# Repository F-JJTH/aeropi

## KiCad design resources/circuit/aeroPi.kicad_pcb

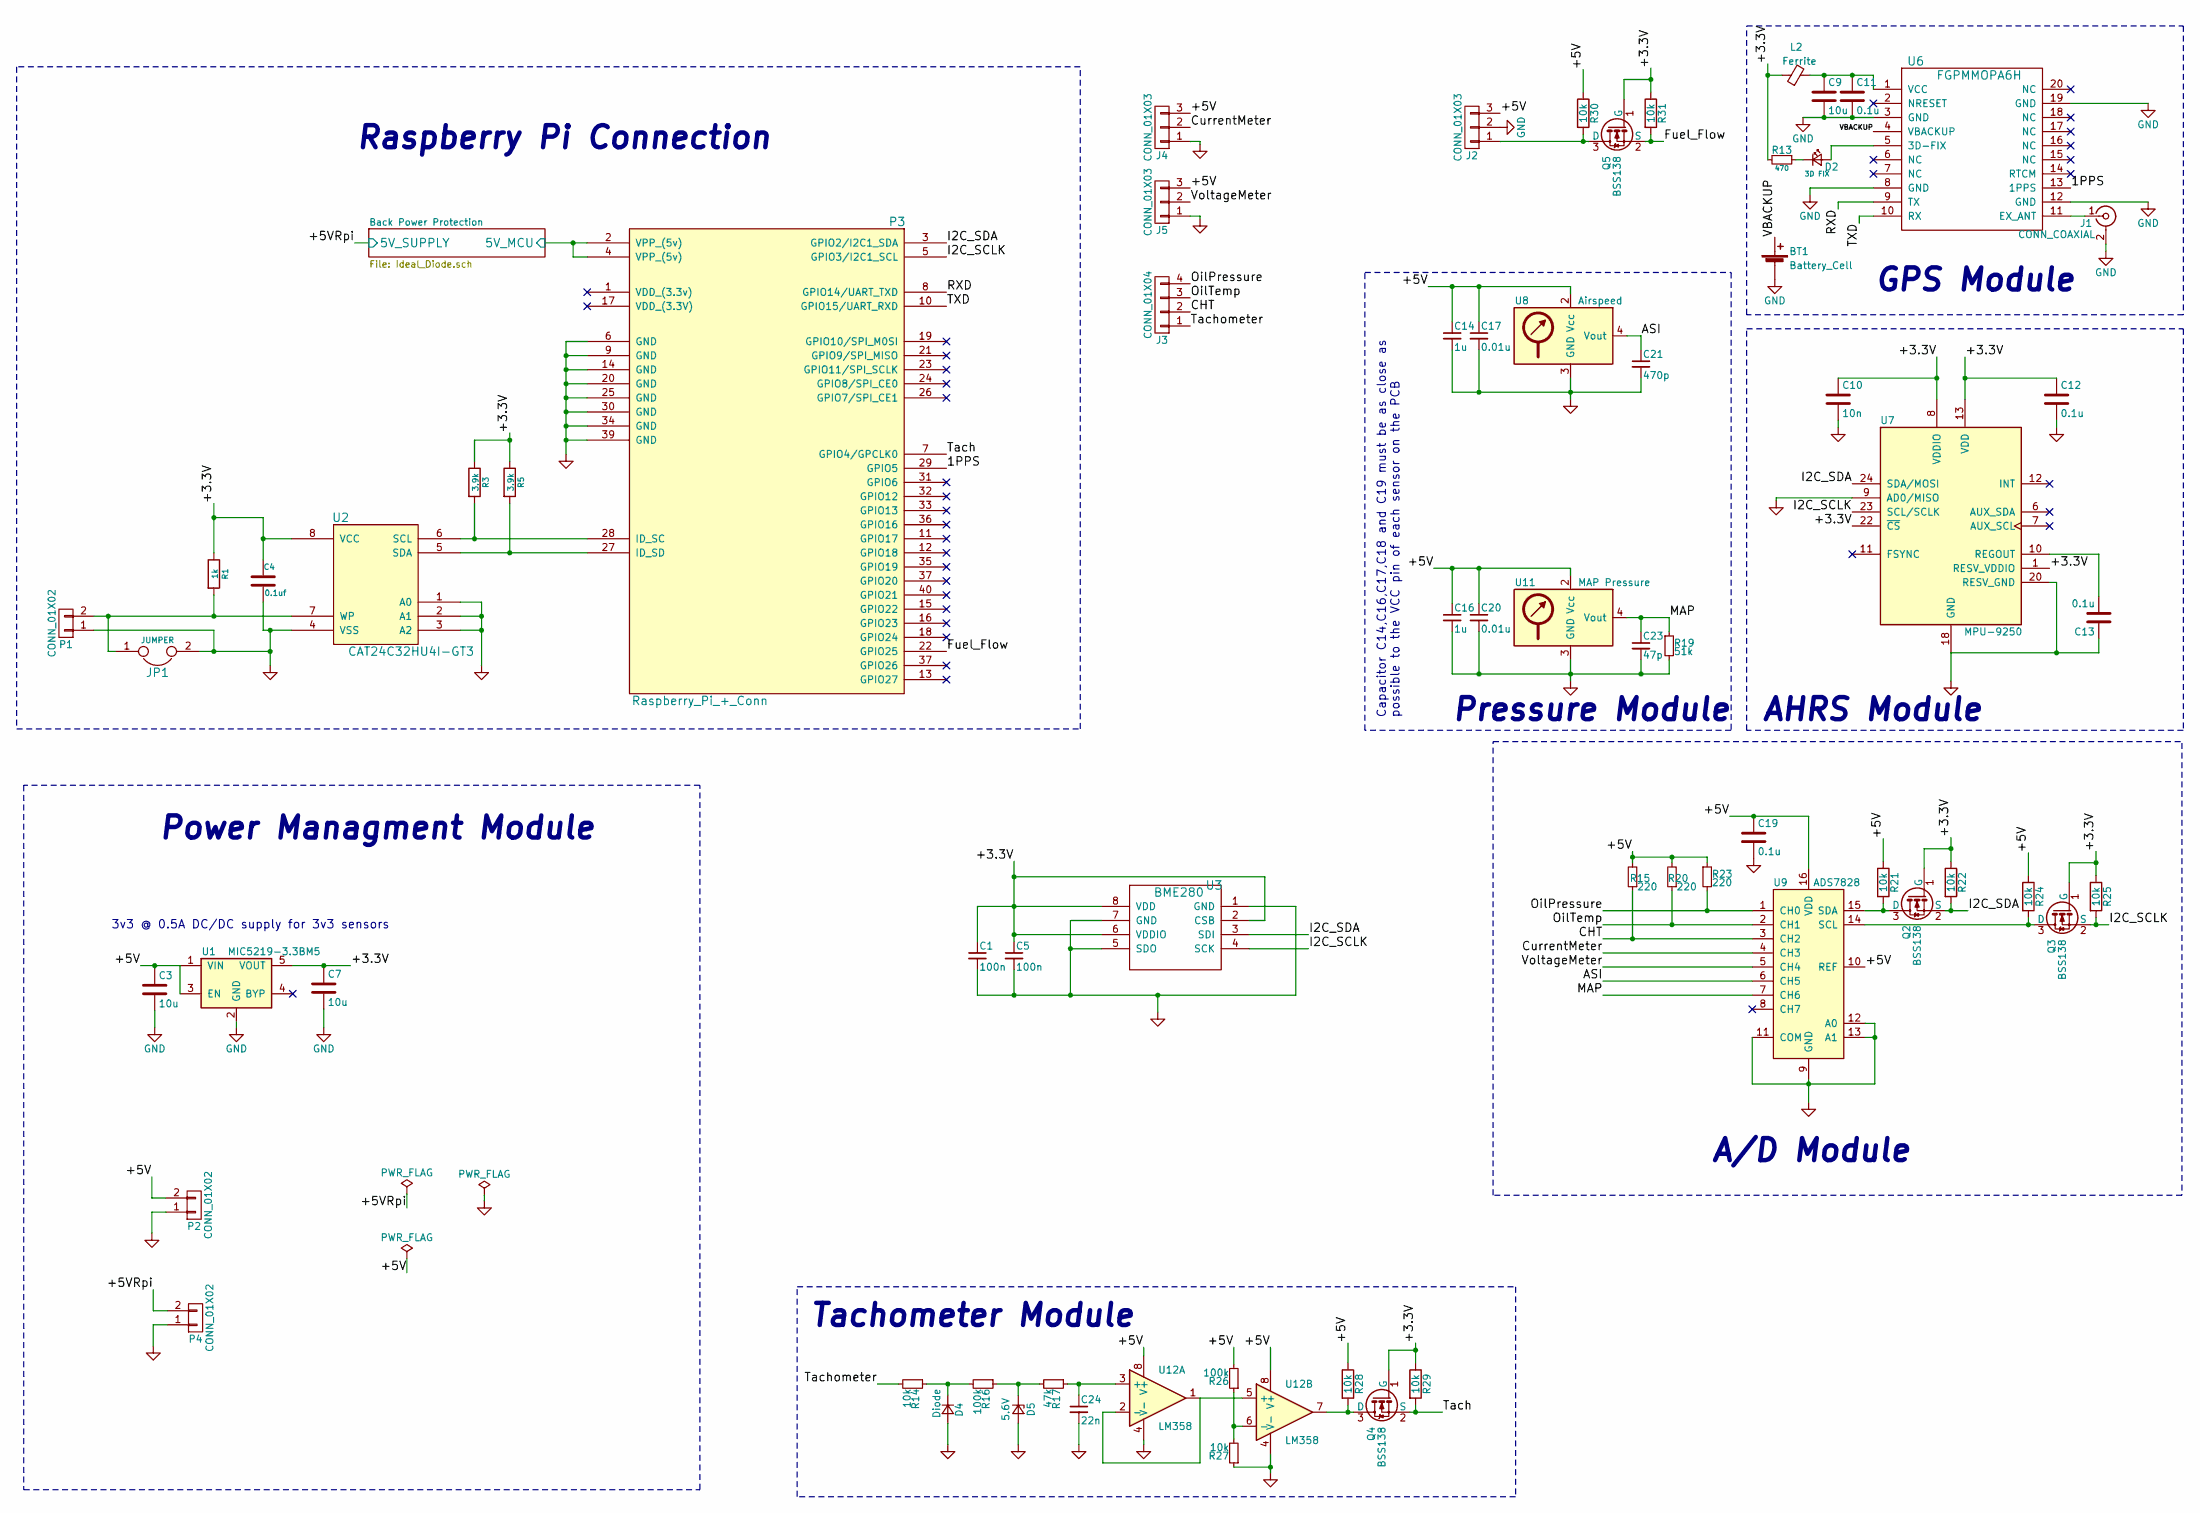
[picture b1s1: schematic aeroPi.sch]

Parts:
BT1: Battery_Cell; CR1220
C1, C5: 100n; C_0603
C3, C7, C9: 10u; C_0603
C4: 0.1uf; C_0603; Mouser Part No. 810-C1005X5R1H104K
C10: 10n; C_0603
C11, C12, C13, C19: 0.1u; C_0603
C14, C16: 1u; C_0603
C17, C20: 0.01u; C_0603
C21: 470p; C_0603
C23: 47p; C_0603
C24: 22n; C_0603
D2: 3D FIX; D_0603
D4: Diode; D_0603
D5: 5.6V; D_SOD-323
J1: CONN_COAXIAL; Molex_Microcoaxial_RF
J2, J4, J5: CONN_01X03; Pin_Header_Straight_1x03_Pitch2.54mm
J3: CONN_01X04; Pin_Header_Straight_1x04_Pitch2.54mm
JP1: JUMPER; R_0603
L2: Ferrite; R_0805
P1: CONN_01X02; Pin_Header_Straight_1x02_Pitch2.54mm
P2, P4: CONN_01X02; Pin_Header_Straight_1x02_Pitch2.54mm; Mouser Part No. 651-1904383
P3: Raspberry_Pi_+_Conn; pin_socket_20x2; Mouser Part No. 517-30340-6002
Q2, Q3, Q4, Q5: BSS138; SOT-23
R1: 1k; R_0603; Mouser Part No. 754-RR0510P-102D
R3, R5: 3.9k; R_0603; Mouser Part No. 71-CRCW04023K90FKED
R13: 470; R_0603
R14, R21, R22, R24, R25, R27, R28, R29, R30, R31: 10k; R_0603
R15, R20, R23: 220; R_0603
R16, R26: 100k; R_0603
R17: 47k; R_0603
R19: 51k; R_0603
U1: MIC5219-3.3BM5; SOT-23-5
U2: CAT24C32HU4I-GT3; tssop-8; Mouser Part No. 698-CAT24C32YI-GT3
U3: BME280
U6: FGPMMOPA6H; PA6H
U7: MPU-9250; QFN-24_3x3mm_Pitch0.4mm
U8: Airspeed; SOIC-8-N
U9: ADS7828; TSSOP-16_4.4x5mm_Pitch0.65mm
U11: MAP Pressure; SOIC-8-N
U12: LM358; SOIC-8_3.9x4.9mm_Pitch1.27mm

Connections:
/1PPS: P3.29 (GPIO5), U6.13 (1PPS)
/+3.3V: C1.1, C4.1, C5.1, C7.1, C10.1, C12.1, L2.1, Q2.1 (G), Q3.1 (G), Q4.1 (G), Q5.1 (G), R1.1, R3.1, R5.1, R13.2, R22.1, R25.1, R29.1, R31.1, U1.5 (VOUT), U2.8 (VCC), U3.2 (CSB), U3.6 (VDDIO), U3.8 (VDD), U7.1 (RESV_VDDIO), U7.8 (VDDIO), U7.13 (VDD), U7.22 (~CS)
/+5V: C3.1, C14.1, C16.1, C17.1, C19.1, C20.1, J2.3, J4.3, J5.3, P2.2, R15.2, R20.2, R21.1, R23.1, R24.1, R26.2, R28.1, R30.1, U1.1 (VIN), U1.3 (EN), U8.2 (Vcc), U9.10 (REF), U9.16 (VDD), U11.2 (Vcc), U12.8 (V+)
/+5VRpi: P4.2; also elsewhere on the board
/ASI: C21.1, U8.4 (Vout), U9.6 (CH5)
/Back Power Protection/5V_MCU: P3.2 (VPP_(5v)), P3.4 (VPP_(5v)); also elsewhere on the board
/CHT: J3.2, R15.1, U9.3 (CH2)
/CurrentMeter: J4.2, U9.4 (CH3)
/Fuel_Flow: P3.22 (GPIO25), Q5.2 (S), R31.2
/I2C_SCLK: P3.5 (GPIO3/I2C1_SCL), Q3.2 (S), R25.2, U3.4 (SCK), U7.23 (SCL/SCLK)
/I2C_SDA: P3.3 (GPIO2/I2C1_SDA), Q2.2 (S), R22.2, U3.3 (SDI), U7.24 (SDA/MOSI)
/MAP: C23.1, R19.1, U9.7 (CH6), U11.4 (Vout)
/OilPressure: J3.4, R23.2, U9.1 (CH0)
/OilTemp: J3.3, R20.1, U9.2 (CH1)
/RXD: P3.8 (GPIO14/UART_TXD), U6.9 (TX)
/TXD: P3.10 (GPIO15/UART_RXD), U6.10 (RX)
/Tach: P3.7 (GPIO4/GPCLK0), Q4.2 (S), R29.2
/Tachometer: J3.1, R14.2
/VBACKUP: BT1.1 (+), U6.4 (VBACKUP)
/VoltageMeter: J5.2, U9.5 (CH4)
GND: BT1.2 (-), C1.2, C3.2, C4.2, C5.2, C7.2, C9.2, C10.2, C11.2, C12.2, C13.1, C14.2, C16.2, C17.2, C19.2, C20.2, C21.2, C23.2, C24.2, D4.2 (A), D5.2 (A), J1.2 (Ext), J2.2, J4.1, J5.1, JP1.2, P1.1, P2.1, P3.6 (GND), P3.9 (GND), P3.14 (GND), P3.20 (GND), P3.25 (GND), P3.30 (GND), P3.34 (GND), P3.39 (GND), P4.1, R19.2, R27.1, U1.2 (GND), U2.1 (A0), U2.2 (A1), U2.3 (A2), U2.4 (VSS), U3.1 (GND), U3.5 (SDO), U3.7 (GND), U6.3 (GND), U6.8 (GND), U6.12 (GND), U6.19 (GND), U7.9 (AD0/MISO), U7.18 (GND), U7.20 (RESV_GND), U8.3 (GND), U9.9 (GND), U9.11 (COM), U9.12 (A0), U9.13 (A1), U11.3 (GND), U12.4 (V-); also elsewhere on the board
unnamed: C9.1, C11.1, L2.2, U6.1 (VCC)
unnamed: C13.2, U7.10 (REGOUT)
unnamed: C24.1, R17.1, U12.3 (+)
unnamed: D2.1 (K), R13.1
unnamed: D2.2 (A), U6.5 (3D-FIX)
unnamed: D4.1 (K), R14.1, R16.2
unnamed: D5.1 (K), R16.1, R17.2
unnamed: J1.1 (In), U6.11 (EX_ANT)
unnamed: J2.1, Q5.3 (D), R30.2
unnamed: JP1.1, P1.2, R1.2, U2.7 (WP)
unnamed: P3.27 (ID_SD), R5.2, U2.5 (SDA)
unnamed: P3.28 (ID_SC), R3.2, U2.6 (SCL)
unnamed: Q2.3 (D), R21.2, U9.15 (SDA)
unnamed: Q3.3 (D), R24.2, U9.14 (SCL)
unnamed: Q4.3 (D), R28.2, U12.7
unnamed: R26.1, R27.2, U12.6 (-)
unnamed: U12.1, U12.2 (-), U12.5 (+)

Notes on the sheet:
Raspberry Pi Connection
Power Managment Module
GPS Module
AHRS Module
A/D Module
Pressure Module
Tachometer Module
Capacitor C14,C16,C17,C18 and C19 must be as close as possible to the VCC pin of each sensor on the PCB
3v3 @ 0.5A DC/DC supply for 3v3 sensors

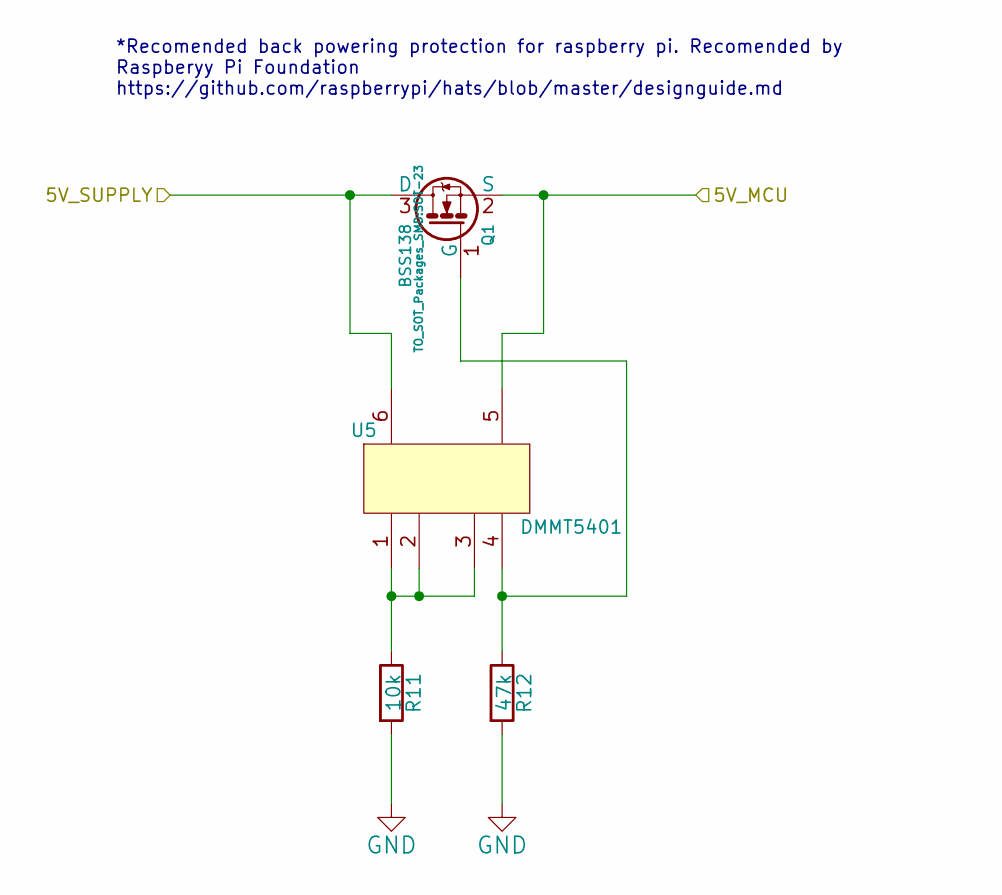
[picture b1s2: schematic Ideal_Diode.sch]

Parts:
Q1: BSS138; SOT-23; Mouser Part No. 621-DMG2305UX-13
R11: 10k; R_0603; Mouser Part No. 71-CRCW0402-10K-E3
R12: 47k; R_0603; Mouser Part No. 667-ERJ-2RKF4702X
U5: DMMT5401; sot23-6; Mouser Part No. 621-DMMT5401-7-F

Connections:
/+5VRpi: Q1.3 (D), U5.6; also elsewhere on the board
/Back Power Protection/5V_MCU: Q1.2 (S), U5.5; also elsewhere on the board
GND: R11.2, R12.2; also elsewhere on the board
unnamed: Q1.1 (G), R12.1, U5.4
unnamed: R11.1, U5.1, U5.2, U5.3

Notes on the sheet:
*Recomended back powering protection for raspberry pi. Recomended by Raspberyy Pi Foundation https://github.com/raspberrypi/hats/blob/master/designguide.md

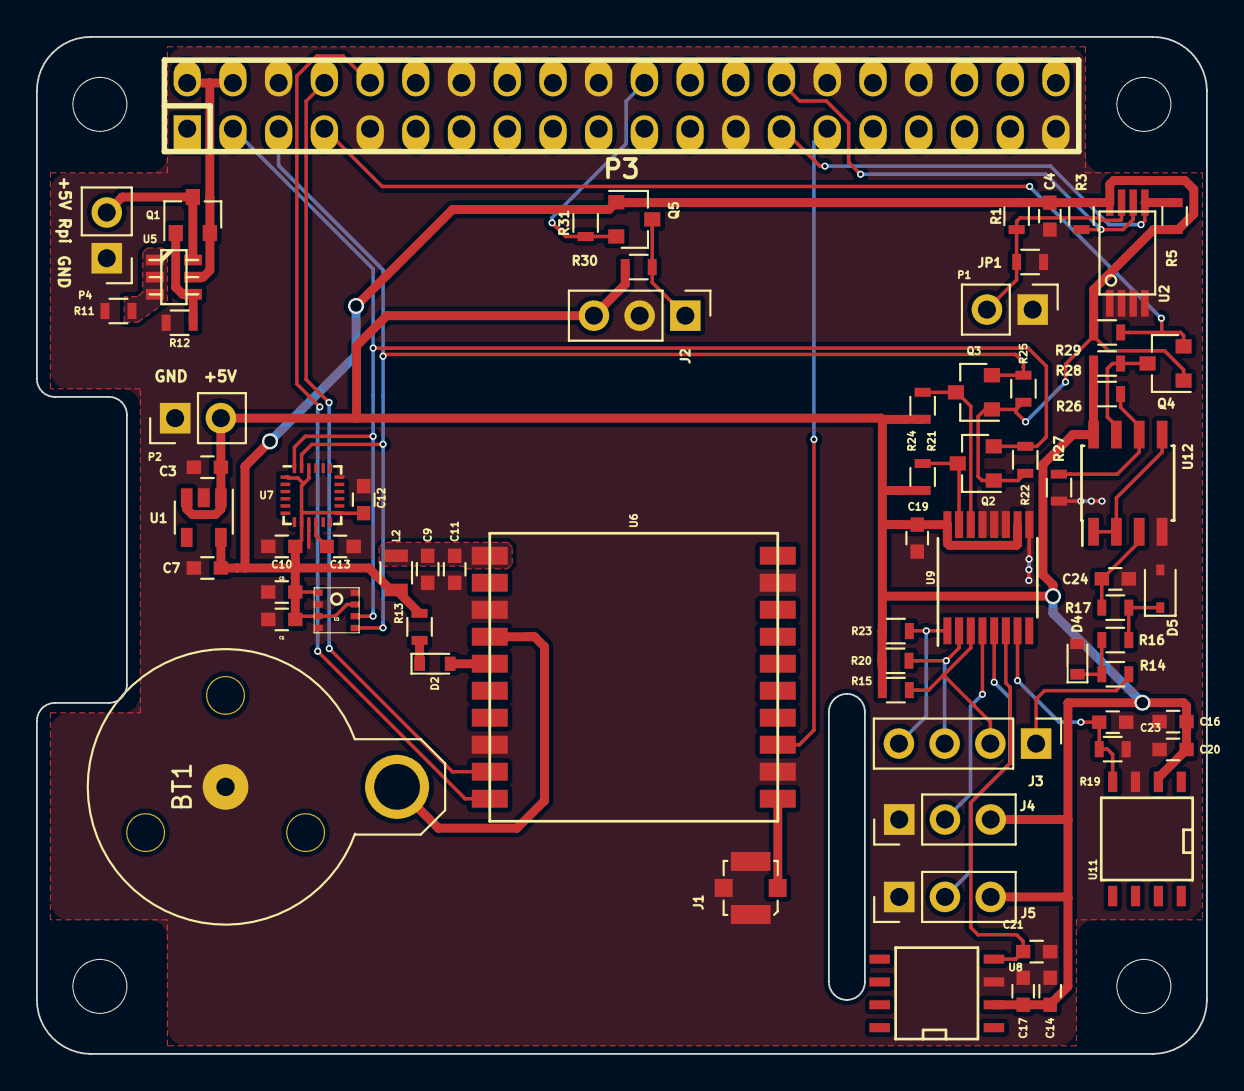
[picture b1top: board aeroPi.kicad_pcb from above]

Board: 2 copper layers, 65.0 x 56.5 mm, 75 parts (0 on the bottom side), 40 nets.

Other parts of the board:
M0, M1, M2, M3: MountingHole_3mm

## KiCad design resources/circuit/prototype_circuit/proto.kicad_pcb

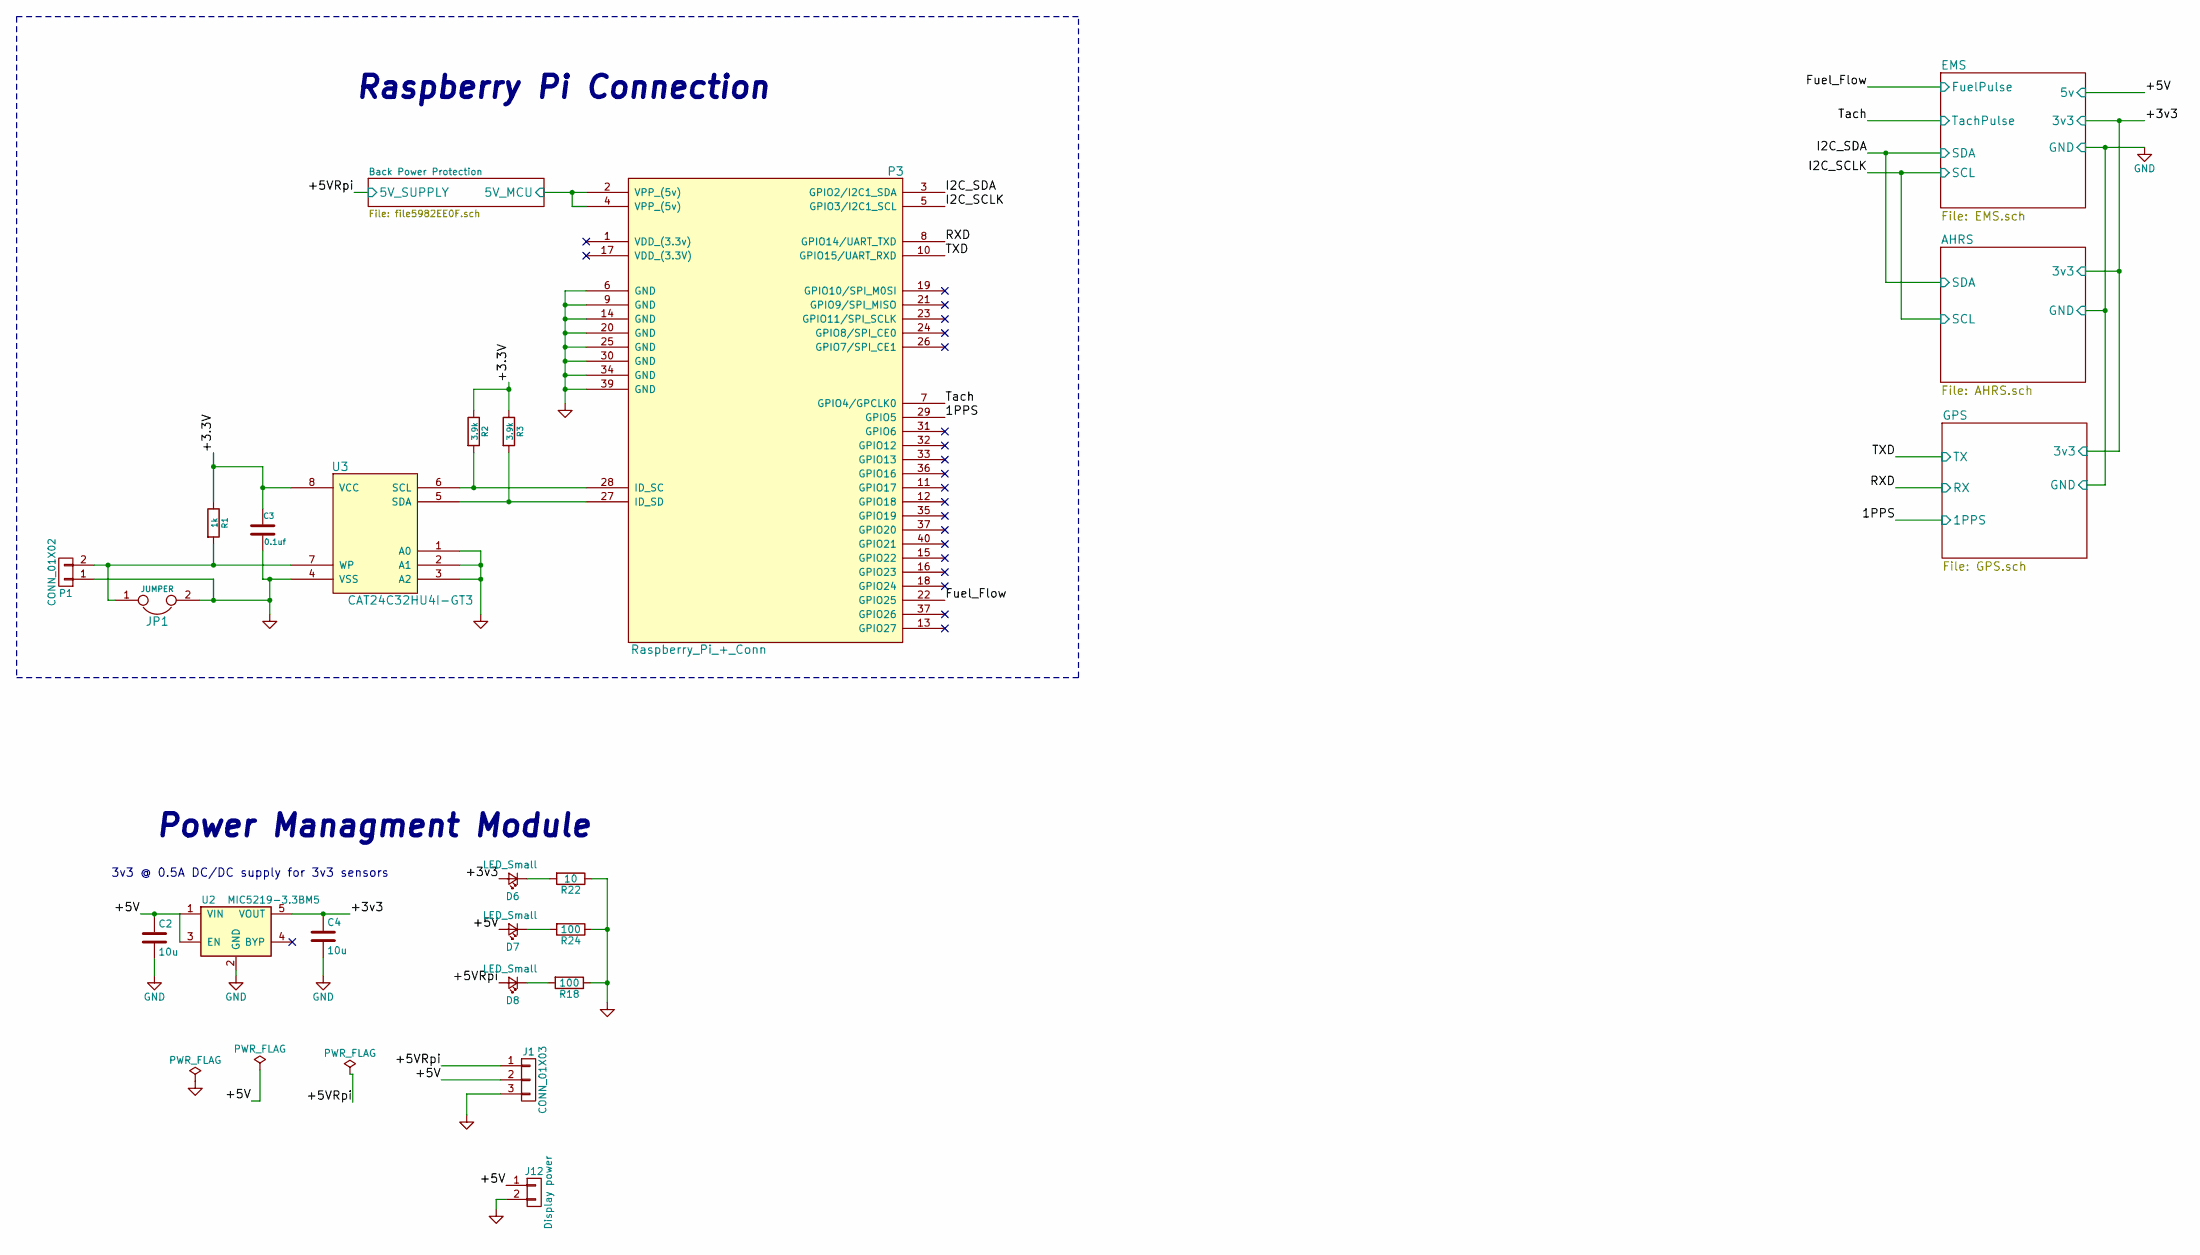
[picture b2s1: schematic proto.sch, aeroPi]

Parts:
C2, C4: 10u; C_0603
C3: 0.1uf; C_0603; Mouser Part No. 810-C1005X5R1H104K
D6, D7, D8: LED_Small; LED_0805
J1: CONN_01X03; Pin_Header_Straight_1x03_Pitch2.54mm
J12: Display power; Pin_Header_Straight_1x02_Pitch2.54mm
JP1: JUMPER; R_0603
P1: CONN_01X02; pin_strip_2
P3: Raspberry_Pi_+_Conn; vasch_strip_20x2; Mouser Part No. 517-30340-6002
R1: 1k; R_0603; Mouser Part No. 754-RR0510P-102D
R2, R3: 3.9k; R_0603; Mouser Part No. 71-CRCW04023K90FKED
R18, R24: 100; R_0603
R22: 10; R_0603
U2: MIC5219-3.3BM5; SOT-23-5
U3: CAT24C32HU4I-GT3; tssop-8; Mouser Part No. 698-CAT24C32YI-GT3

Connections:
/1PPS: P3.29 (GPIO5); also elsewhere on the board
/+3.3V: C3.1, R1.1, R2.1, R3.1, U3.8 (VCC)
/+3v3: C4.1, D6.2 (A), U2.5 (VOUT); also elsewhere on the board
/+5V: C2.1, D7.2 (A), J1.2, J12.1, U2.1 (VIN), U2.3 (EN); also elsewhere on the board
/+5VRpi: D8.2 (A), J1.1; also elsewhere on the board
/Back Power Protection/5V_MCU: P3.2 (VPP_(5v)), P3.4 (VPP_(5v)); also elsewhere on the board
/Fuel_Flow: P3.22 (GPIO25); also elsewhere on the board
/I2C_SCLK: P3.5 (GPIO3/I2C1_SCL); also elsewhere on the board
/I2C_SDA: P3.3 (GPIO2/I2C1_SDA); also elsewhere on the board
/RXD: P3.8 (GPIO14/UART_TXD); also elsewhere on the board
/TXD: P3.10 (GPIO15/UART_RXD); also elsewhere on the board
/Tach: P3.7 (GPIO4/GPCLK0); also elsewhere on the board
GND: C2.2, C3.2, C4.2, J1.3, J12.2, JP1.2, P1.1, P3.6 (GND), P3.9 (GND), P3.14 (GND), P3.20 (GND), P3.25 (GND), P3.30 (GND), P3.34 (GND), P3.39 (GND), R18.1, R22.1, R24.1, U2.2 (GND), U3.1 (A0), U3.2 (A1), U3.3 (A2), U3.4 (VSS); also elsewhere on the board
unnamed: D6.1 (K), R22.2
unnamed: D7.1 (K), R24.2
unnamed: D8.1 (K), R18.2
unnamed: JP1.1, P1.2, R1.2, U3.7 (WP)
unnamed: P3.27 (ID_SD), R3.2, U3.5 (SDA)
unnamed: P3.28 (ID_SC), R2.2, U3.6 (SCL)

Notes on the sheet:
Raspberry Pi Connection
Power Managment Module
3v3 @ 0.5A DC/DC supply for 3v3 sensors

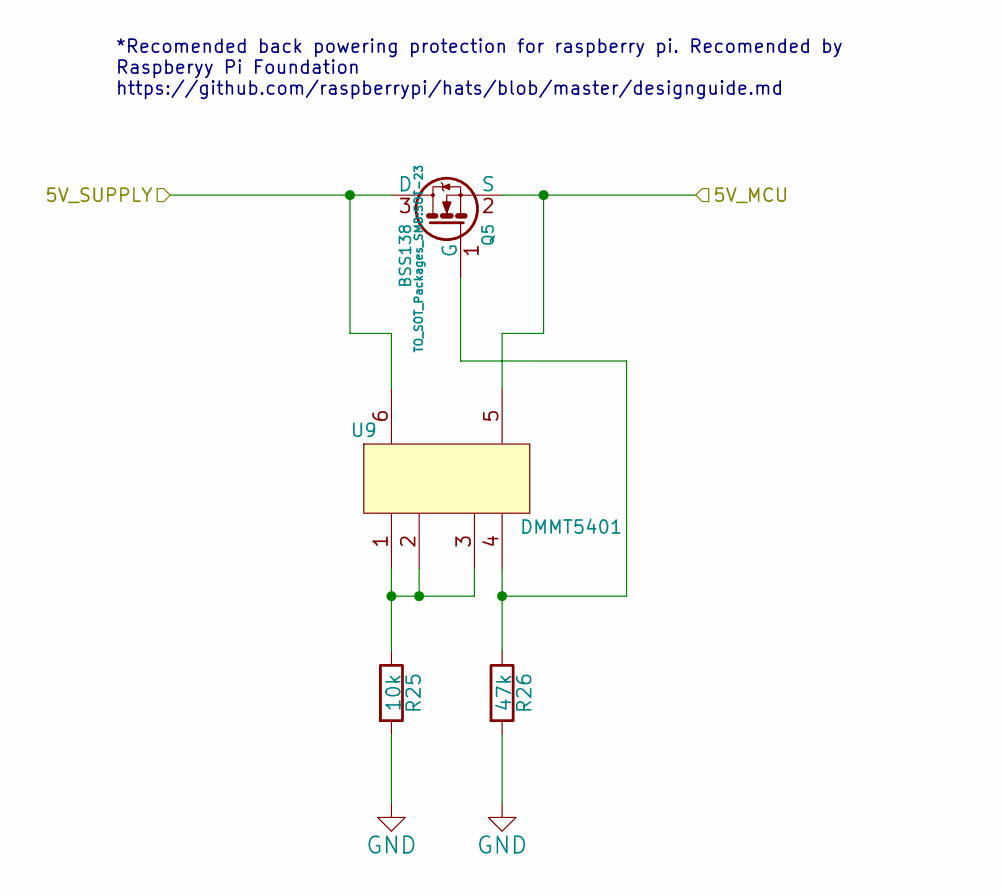
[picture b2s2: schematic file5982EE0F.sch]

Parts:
Q5: BSS138; SOT-23; Mouser Part No. 621-DMG2305UX-13
R25: 10k; R_0603; Mouser Part No. 71-CRCW0402-10K-E3
R26: 47k; R_0603; Mouser Part No. 667-ERJ-2RKF4702X
U9: DMMT5401; sot23-6; Mouser Part No. 621-DMMT5401-7-F

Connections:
/+5VRpi: Q5.3 (D), U9.6; also elsewhere on the board
/Back Power Protection/5V_MCU: Q5.2 (S), U9.5; also elsewhere on the board
GND: R25.2, R26.2; also elsewhere on the board
unnamed: Q5.1 (G), R26.1, U9.4
unnamed: R25.1, U9.1, U9.2, U9.3

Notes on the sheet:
*Recomended back powering protection for raspberry pi. Recomended by Raspberyy Pi Foundation https://github.com/raspberrypi/hats/blob/master/designguide.md

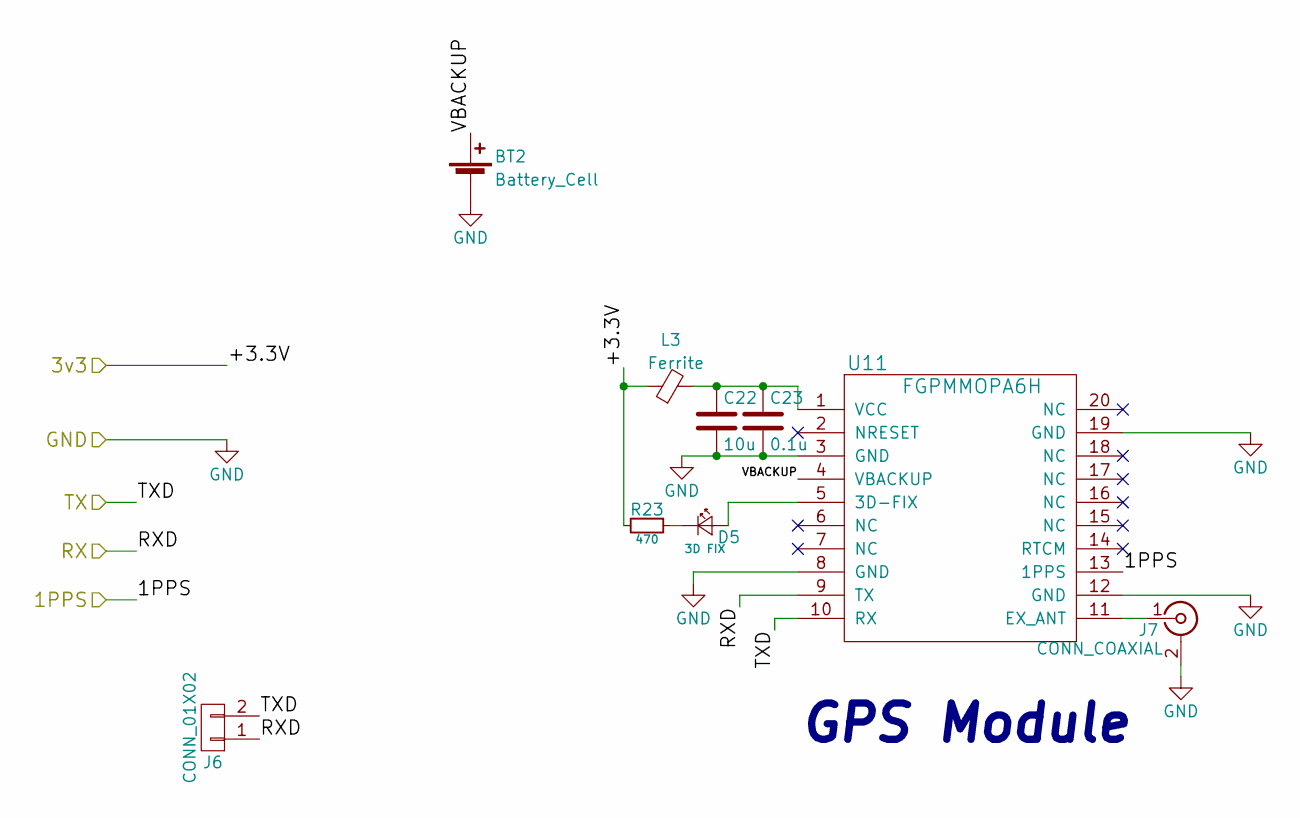
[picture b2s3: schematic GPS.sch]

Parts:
BT2: Battery_Cell; Keystone_3000_1x12mm-CoinCell
C22: 10u; C_0603
C23: 0.1u; C_0603
D5: 3D FIX; D_0603
J6: CONN_01X02; Pin_Header_Straight_1x02_Pitch2.54mm
J7: CONN_COAXIAL; Molex_Microcoaxial_RF
L3: Ferrite; R_0805
R23: 470; R_0603
U11: FGPMMOPA6H; PA6H

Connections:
/1PPS: U11.13 (1PPS); also elsewhere on the board
/+3v3: L3.1, R23.2; also elsewhere on the board
/GPS/VBACKUP: BT2.1 (+), U11.4 (VBACKUP)
/RXD: J6.1, U11.9 (TX); also elsewhere on the board
/TXD: J6.2, U11.10 (RX); also elsewhere on the board
GND: BT2.2 (-), C22.2, C23.2, J7.2 (Ext), U11.3 (GND), U11.8 (GND), U11.12 (GND), U11.19 (GND); also elsewhere on the board
unnamed: C22.1, C23.1, L3.2, U11.1 (VCC)
unnamed: D5.1 (K), R23.1
unnamed: D5.2 (A), U11.5 (3D-FIX)
unnamed: J7.1 (In), U11.11 (EX_ANT)

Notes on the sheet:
GPS Module

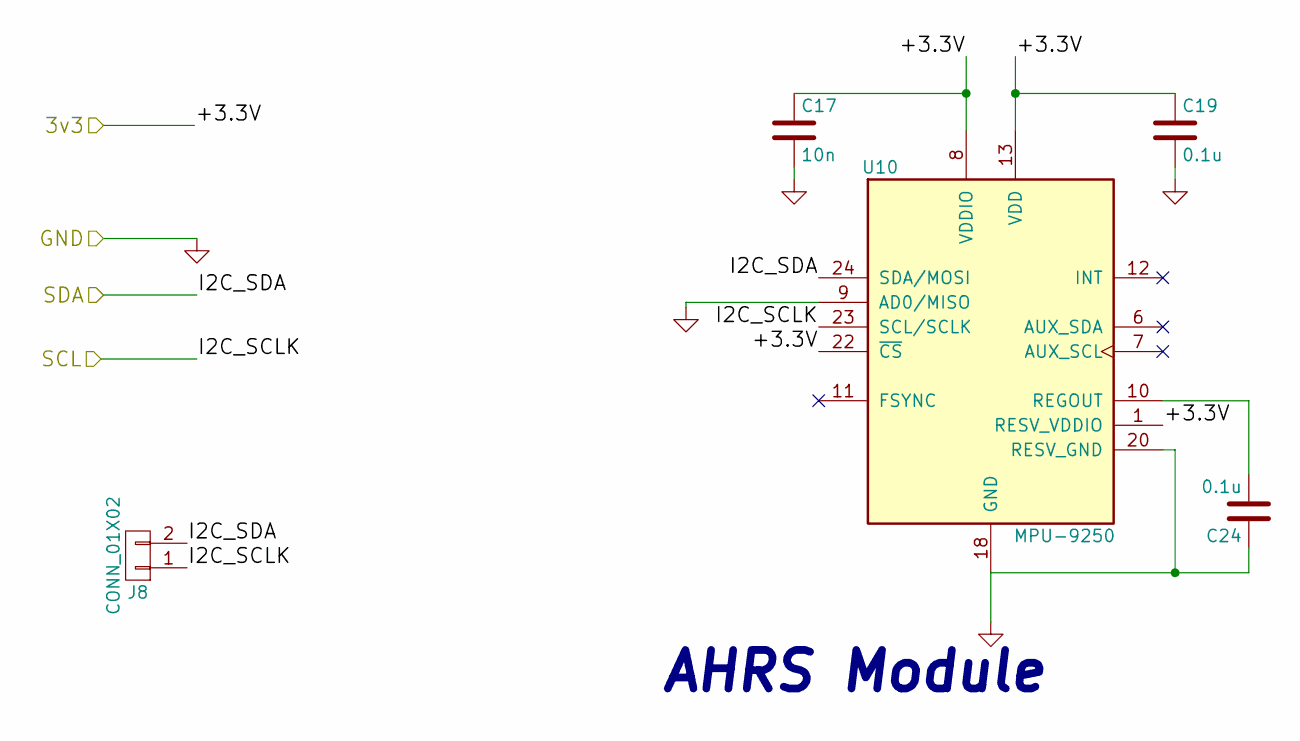
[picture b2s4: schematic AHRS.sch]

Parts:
C17: 10n; C_0603
C19, C24: 0.1u; C_0603
J8: CONN_01X02; Pin_Header_Straight_1x02_Pitch2.54mm
U10: MPU-9250; QFN-24_3x3mm_Pitch0.4mm

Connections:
/+3v3: C17.1, C19.1, U10.1 (RESV_VDDIO), U10.8 (VDDIO), U10.13 (VDD), U10.22 (~CS); also elsewhere on the board
/I2C_SCLK: J8.1, U10.23 (SCL/SCLK); also elsewhere on the board
/I2C_SDA: J8.2, U10.24 (SDA/MOSI); also elsewhere on the board
GND: C17.2, C19.2, C24.1, U10.9 (AD0/MISO), U10.18 (GND), U10.20 (RESV_GND); also elsewhere on the board
unnamed: C24.2, U10.10 (REGOUT)

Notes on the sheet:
AHRS Module

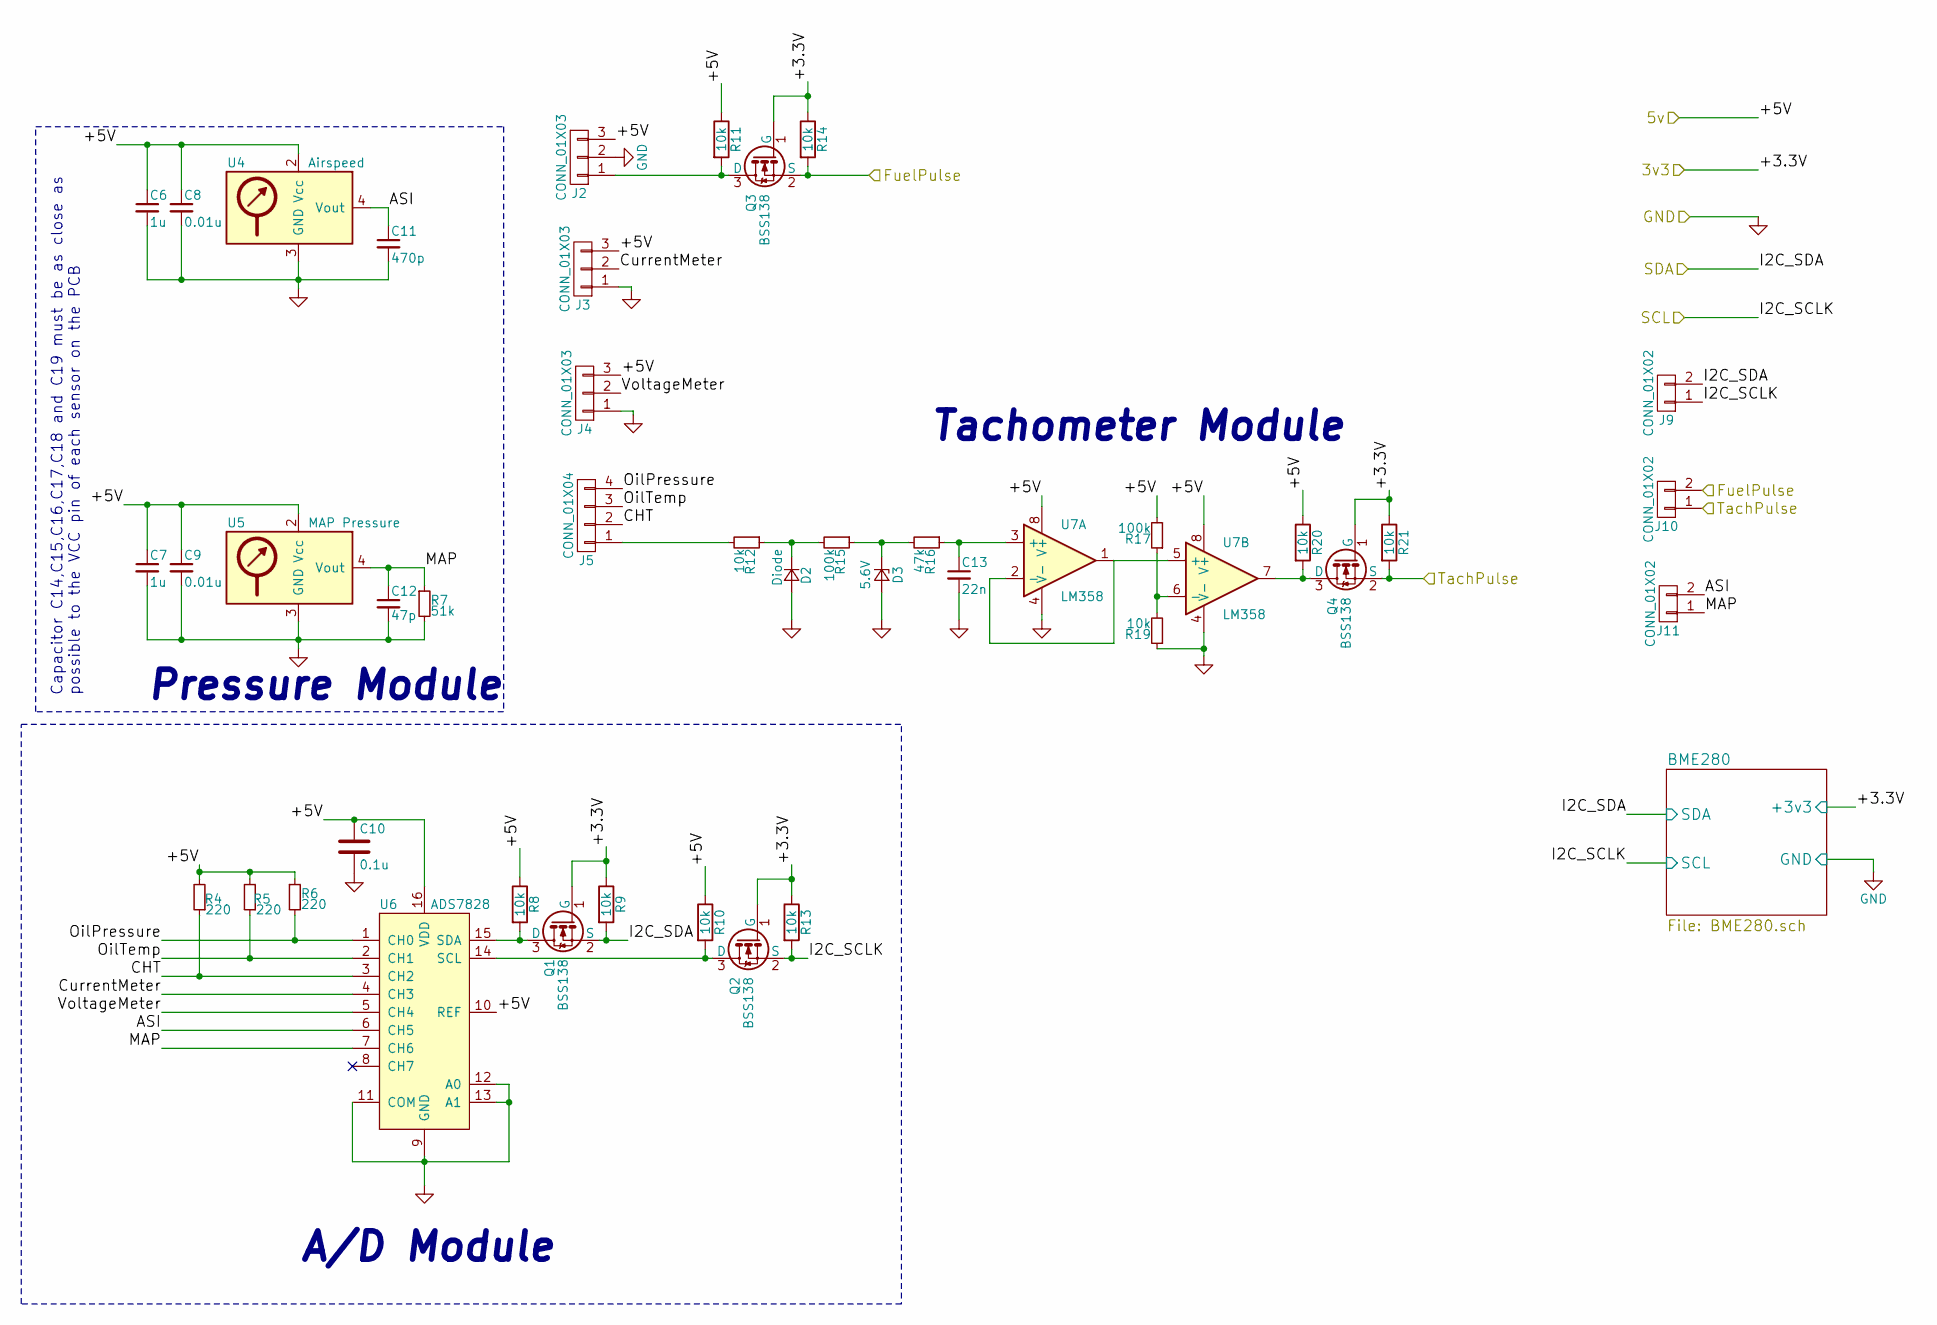
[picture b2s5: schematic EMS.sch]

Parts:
C6, C7: 1u; C_0603
C8, C9: 0.01u; C_0603
C10: 0.1u; C_0603
C11: 470p; C_0603
C12: 47p; C_0603
C13: 22n; C_0603
D2: Diode; D_0603
D3: 5.6V; D_SOD-323
J2, J3, J4: CONN_01X03; Pin_Header_Straight_1x03_Pitch2.54mm
J5: CONN_01X04; Pin_Header_Straight_1x04_Pitch2.54mm
J9, J10, J11: CONN_01X02; Pin_Header_Straight_1x02_Pitch2.54mm
Q1, Q2, Q3, Q4: BSS138; SOT-23
R4, R5, R6: 220; R_0603
R7: 51k; R_0603
R8, R9, R10, R11, R12, R13, R14, R19, R20, R21: 10k; R_0603
R15, R17: 100k; R_0603
R16: 47k; R_0603
U4: Airspeed; SOIC-8-N
U5: MAP Pressure; SOIC-8-N
U6: ADS7828; TSSOP-16_4.4x5mm_Pitch0.65mm
U7: LM358; SOIC-8_3.9x4.9mm_Pitch1.27mm

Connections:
/+3v3: Q1.1 (G), Q2.1 (G), Q3.1 (G), Q4.1 (G), R9.1, R13.1, R14.1, R21.1; also elsewhere on the board
/+5V: C6.1, C7.1, C8.1, C9.1, C10.1, J2.3, J3.3, J4.3, R4.2, R5.2, R6.1, R8.1, R10.1, R11.1, R17.2, R20.1, U4.2 (Vcc), U5.2 (Vcc), U6.10 (REF), U6.16 (VDD), U7.8 (V+); also elsewhere on the board
/EMS/ASI: C11.1, J11.2, U4.4 (Vout), U6.6 (CH5)
/EMS/CHT: J5.2, R4.1, U6.3 (CH2)
/EMS/CurrentMeter: J3.2, U6.4 (CH3)
/EMS/MAP: C12.1, J11.1, R7.1, U5.4 (Vout), U6.7 (CH6)
/EMS/OilPressure: J5.4, R6.2, U6.1 (CH0)
/EMS/OilTemp: J5.3, R5.1, U6.2 (CH1)
/EMS/VoltageMeter: J4.2, U6.5 (CH4)
/Fuel_Flow: J10.2, Q3.2 (S), R14.2; also elsewhere on the board
/I2C_SCLK: J9.1, Q2.2 (S), R13.2; also elsewhere on the board
/I2C_SDA: J9.2, Q1.2 (S), R9.2; also elsewhere on the board
/Tach: J10.1, Q4.2 (S), R21.2; also elsewhere on the board
GND: C6.2, C7.2, C8.2, C9.2, C10.2, C11.2, C12.2, C13.2, D2.2 (A), D3.2 (A), J2.2, J3.1, J4.1, R7.2, R19.1, U4.3 (GND), U5.3 (GND), U6.9 (GND), U6.11 (COM), U6.12 (A0), U6.13 (A1), U7.4 (V-); also elsewhere on the board
unnamed: C13.1, R16.1, U7.3 (+)
unnamed: D2.1 (K), R12.1, R15.2
unnamed: D3.1 (K), R15.1, R16.2
unnamed: J2.1, Q3.3 (D), R11.2
unnamed: J5.1, R12.2
unnamed: Q1.3 (D), R8.2, U6.15 (SDA)
unnamed: Q2.3 (D), R10.2, U6.14 (SCL)
unnamed: Q4.3 (D), R20.2, U7.7
unnamed: R17.1, R19.2, U7.6 (-)
unnamed: U7.1, U7.2 (-), U7.5 (+)

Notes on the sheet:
A/D Module
Pressure Module
Capacitor C14,C15,C16,C17,C18 and C19 must be as close as possible to the VCC pin of each sensor on the PCB
Tachometer Module

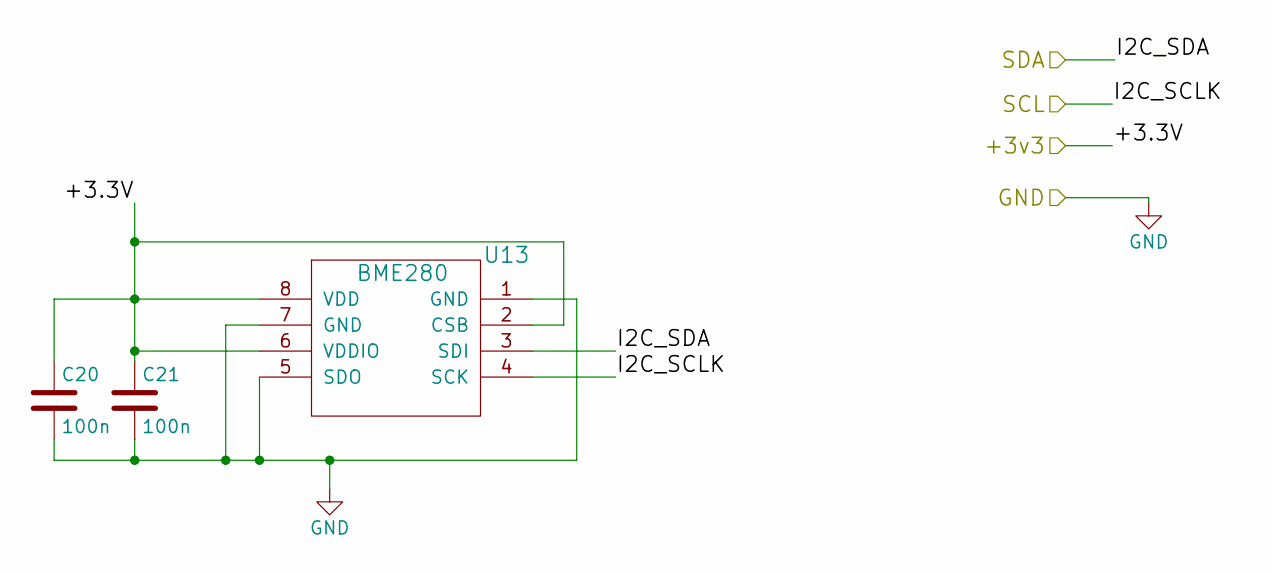
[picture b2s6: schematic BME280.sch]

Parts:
C20, C21: 100n; C_0603
U13: BME280

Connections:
/+3v3: C20.1, C21.1, U13.2 (CSB), U13.6 (VDDIO), U13.8 (VDD); also elsewhere on the board
/I2C_SCLK: U13.4 (SCK); also elsewhere on the board
/I2C_SDA: U13.3 (SDI); also elsewhere on the board
GND: C20.2, C21.2, U13.1 (GND), U13.5 (SDO), U13.7 (GND); also elsewhere on the board

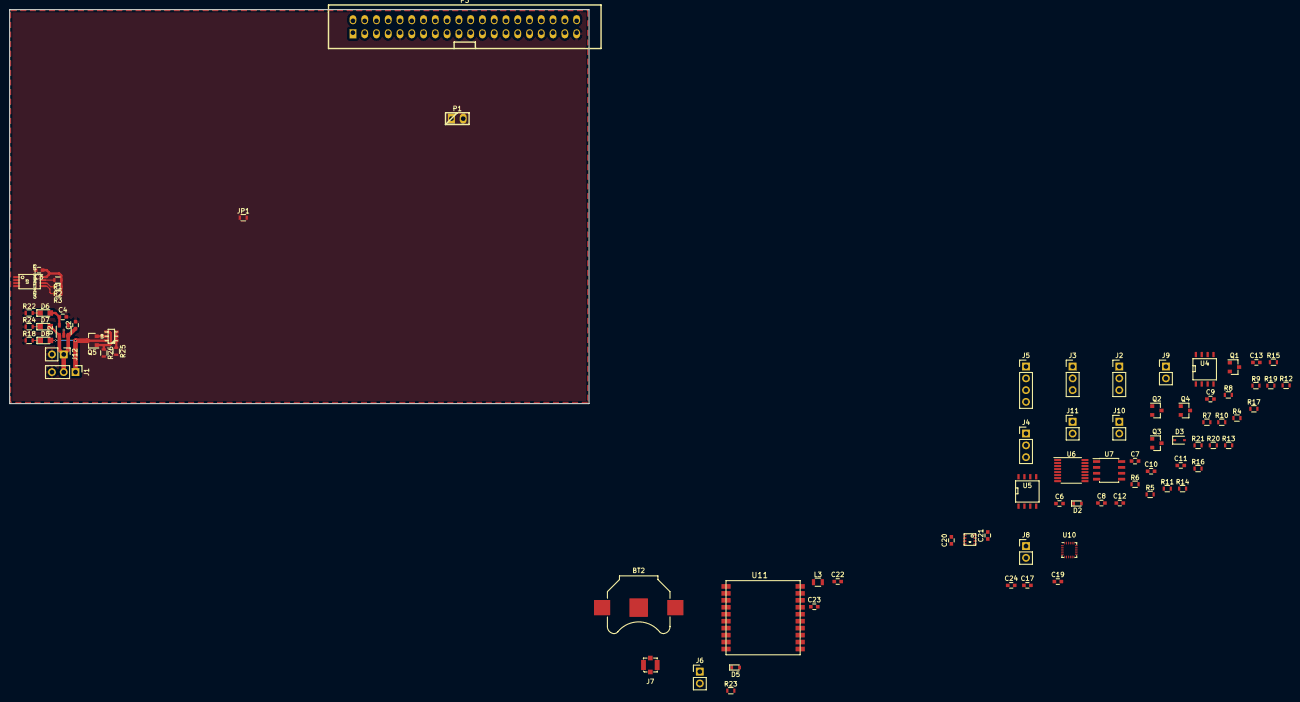
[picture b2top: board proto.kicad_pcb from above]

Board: 2 copper layers, 125.0 x 85.0 mm, 82 parts (0 on the bottom side), 44 nets.

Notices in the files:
resources/circuit/aeroPi.kicad_pcb:
License: CERN OHL V1.2
